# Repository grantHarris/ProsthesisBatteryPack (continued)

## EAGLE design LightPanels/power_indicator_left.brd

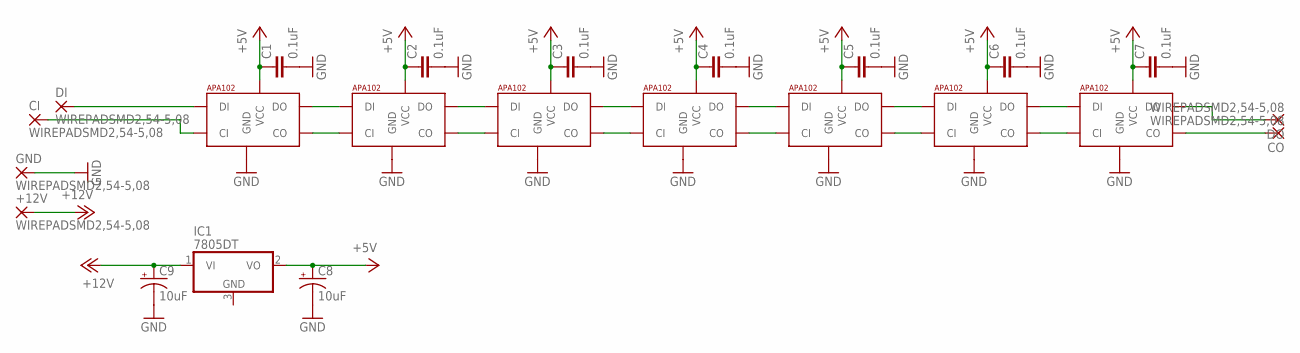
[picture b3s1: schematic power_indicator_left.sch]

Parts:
+12V: WIREPADSMD2,54-5,08; SMD2,54-5,08
C1, C2, C3, C4, C5, C6, C7: 0.1uF; 0603-CAP
C8, C9: 10uF; EIA3216
CI: WIREPADSMD2,54-5,08; SMD2,54-5,08
CO: WIREPADSMD2,54-5,08; SMD2,54-5,08
DI: WIREPADSMD2,54-5,08; SMD2,54-5,08
DO: WIREPADSMD2,54-5,08; SMD2,54-5,08
GND: WIREPADSMD2,54-5,08; SMD2,54-5,08
IC1: 7805DT; TO252
U$1, U$2, U$3, U$4, U$5, U$6, U$7: APA1025050; APA102_5050

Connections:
+5V: C1.1, C2.1, C3.1, C4.1, C5.1, C6.1, C7.1, C8.A (+), IC1.2 (VO), U$1.1 (VCC), U$2.1 (VCC), U$3.1 (VCC), U$4.1 (VCC), U$5.1 (VCC), U$6.1 (VCC), U$7.1 (VCC)
+12V: +12V.1, C9.A (+), IC1.1 (VI)
GND: C1.2, C2.2, C3.2, C4.2, C5.2, C6.2, C7.2, C8.C (-), C9.C (-), GND.1, U$1.6 (GND), U$2.6 (GND), U$3.6 (GND), U$4.6 (GND), U$5.6 (GND), U$6.6 (GND), U$7.6 (GND)
unnamed: U$1.2 (CO), U$2.5 (CI)
unnamed: U$1.3 (DO), U$2.4 (DI)
unnamed: U$2.2 (CO), U$3.5 (CI)
unnamed: U$2.3 (DO), U$3.4 (DI)
unnamed: U$3.2 (CO), U$4.5 (CI)
unnamed: U$3.3 (DO), U$4.4 (DI)
unnamed: U$4.2 (CO), U$5.5 (CI)
unnamed: U$4.3 (DO), U$5.4 (DI)
unnamed: U$5.2 (CO), U$6.5 (CI)
unnamed: U$5.3 (DO), U$6.4 (DI)
unnamed: U$6.2 (CO), U$7.5 (CI)
unnamed: U$6.3 (DO), U$7.4 (DI)
unnamed: CO.1, U$7.2 (CO)
unnamed: DO.1, U$7.3 (DO)
unnamed: DI.1, U$1.4 (DI)
unnamed: CI.1, U$1.5 (CI)

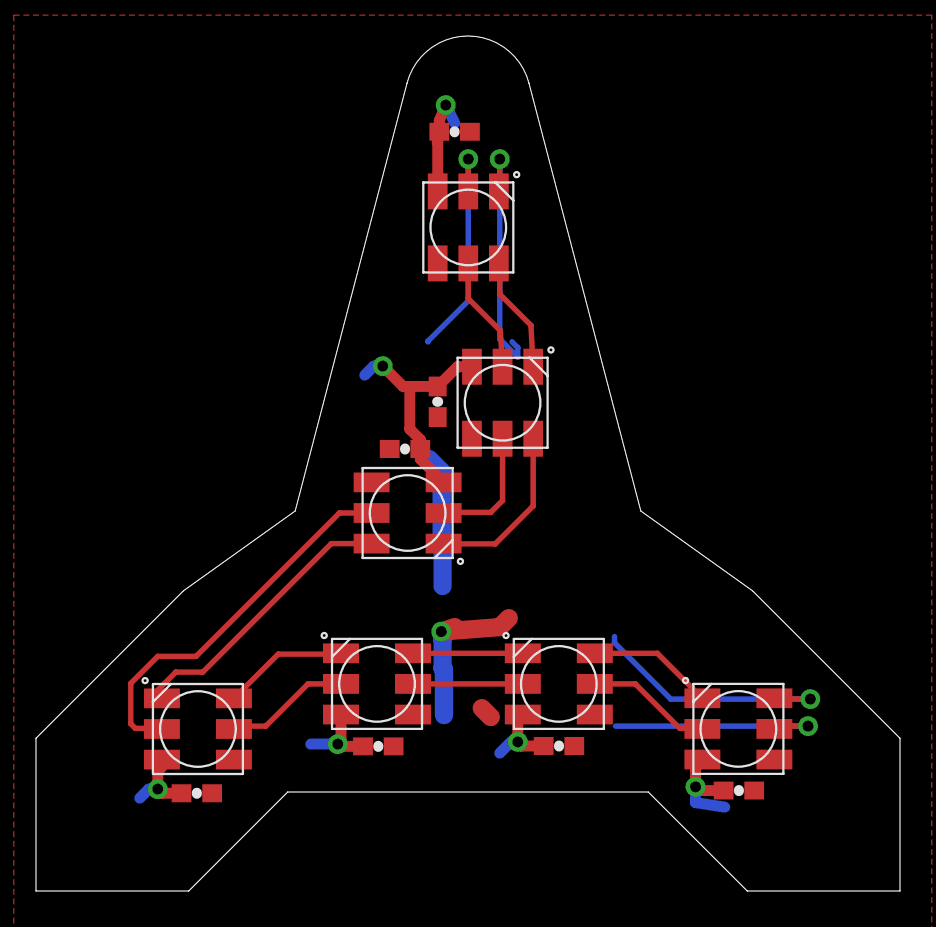
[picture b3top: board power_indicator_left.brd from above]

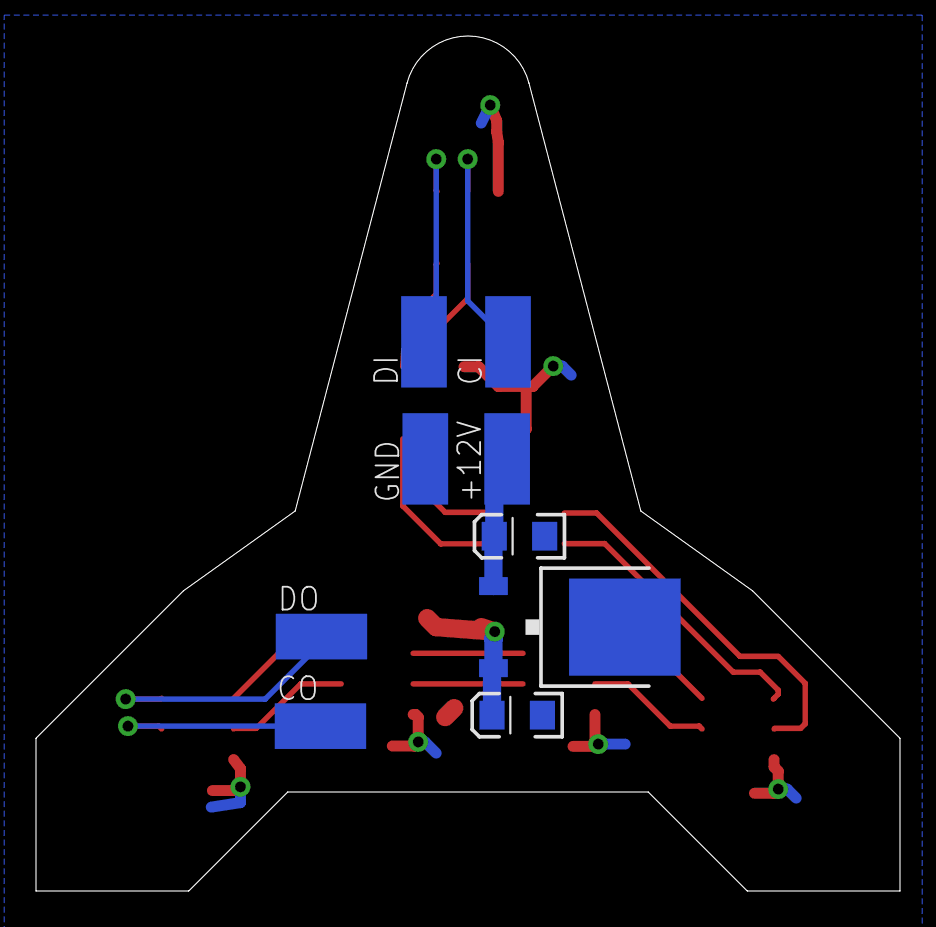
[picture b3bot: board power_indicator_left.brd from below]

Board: 2 copper layers, 48.0 x 47.5 mm, 23 parts (9 on the bottom side), 19 nets.

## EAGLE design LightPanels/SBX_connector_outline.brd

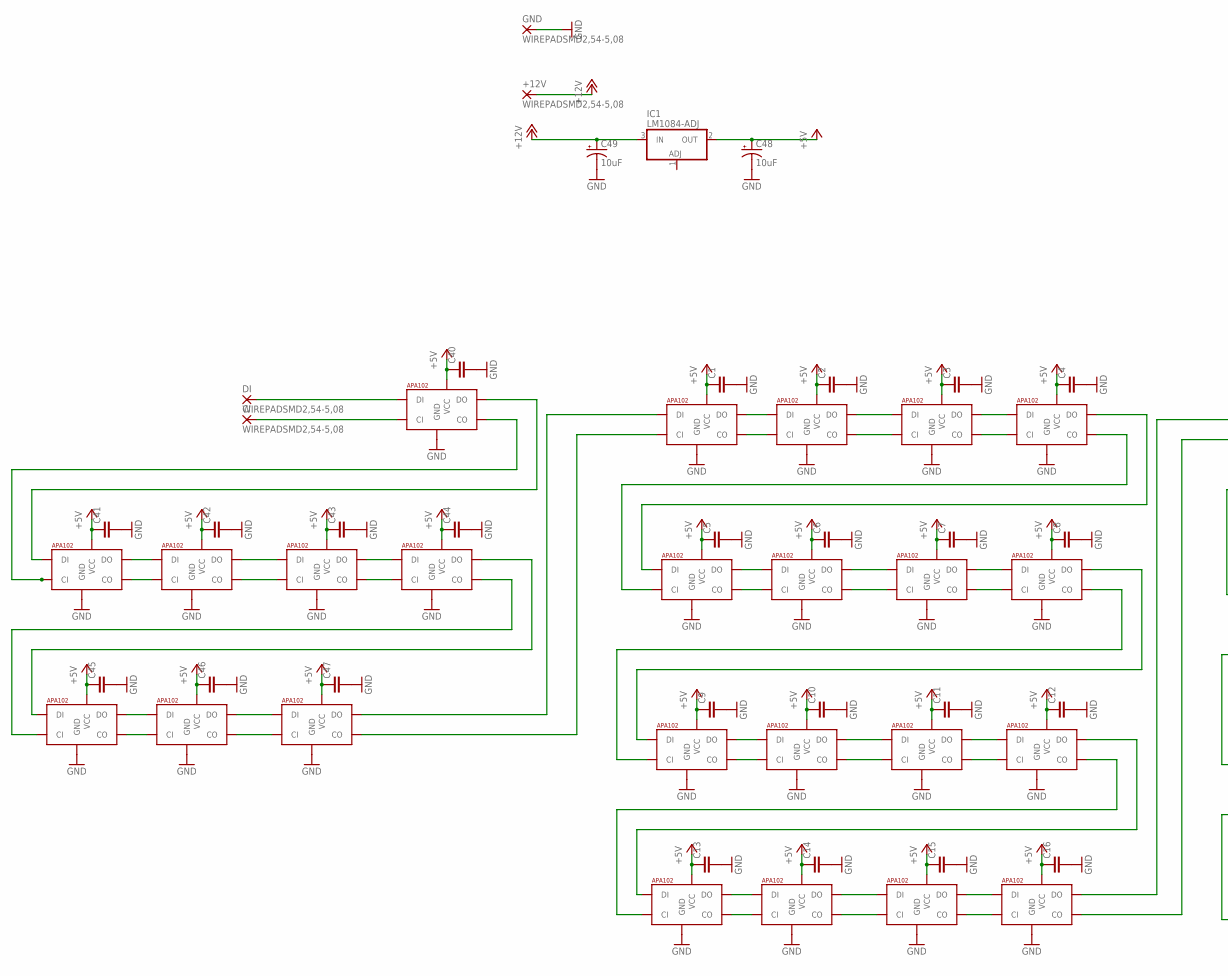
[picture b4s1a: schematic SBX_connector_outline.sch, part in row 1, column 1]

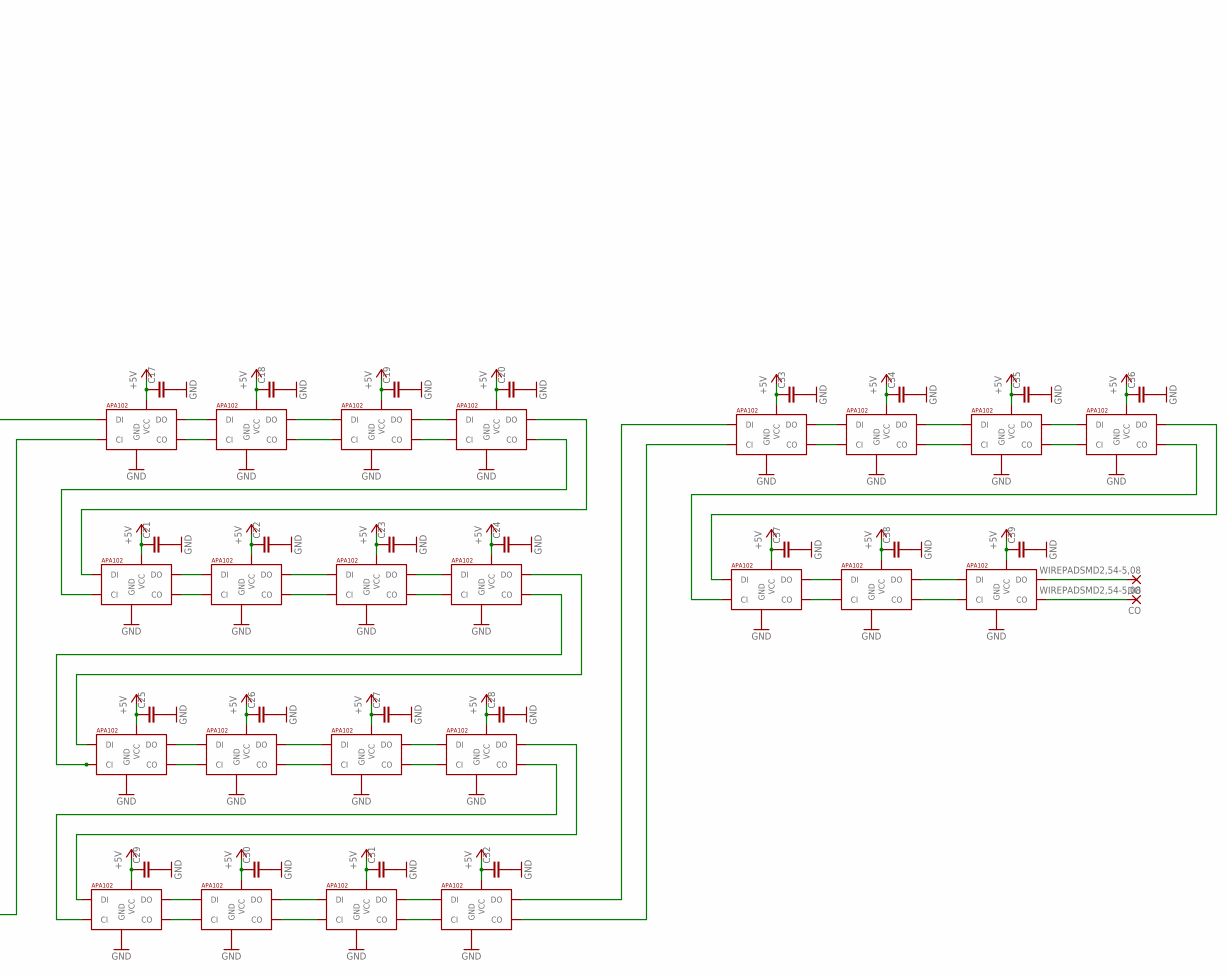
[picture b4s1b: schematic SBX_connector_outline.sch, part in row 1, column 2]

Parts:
+12V: WIREPADSMD2,54-5,08; SMD2,54-5,08
C1, C2, C3, C4, C5, C6, C7, C8, C9, C10, C11, C12, C13, C14, C15, C16, C17, C18, C19, C20, C21, C22, C23, C24, C25, C26, C27, C28, C29, C30, C31, C32, C33, C34, C35, C36, C37, C38, C39, C40, C41, C42, C43, C44, C45, C46, C47: CAP0603-CAP; 0603-CAP
C48, C49: 10uF; EIA3216
CI: WIREPADSMD2,54-5,08; SMD2,54-5,08
CO: WIREPADSMD2,54-5,08; SMD2,54-5,08
DI: WIREPADSMD2,54-5,08; SMD2,54-5,08
DO: WIREPADSMD2,54-5,08; SMD2,54-5,08
GND: WIREPADSMD2,54-5,08; SMD2,54-5,08
IC1: LM1084-ADJ; TO263-3
U$1, U$2, U$3, U$4, U$5, U$6, U$7, U$8, U$9, U$10, U$11, U$12, U$13, U$14, U$15, U$16, U$17, U$18, U$19, U$20, U$21, U$22, U$23, U$24, U$25, U$26, U$27, U$28, U$29, U$30, U$31, U$32, U$33, U$34, U$35, U$36, U$37, U$38, U$39, U$40, U$41, U$42, U$43, U$44, U$45, U$46, U$47: APA1025050; APA102_5050

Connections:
+5V: C1.1, C2.1, C3.1, C4.1, C5.1, C6.1, C7.1, C8.1, C9.1, C10.1, C11.1, C12.1, C13.1, C14.1, C15.1, C16.1, C17.1, C18.1, C19.1, C20.1, C21.1, C22.1, C23.1, C24.1, C25.1, C26.1, C27.1, C28.1, C29.1, C30.1, C31.1, C32.1, C33.1, C34.1, C35.1, C36.1, C37.1, C38.1, C39.1, C40.1, C41.1, C42.1, C43.1, C44.1, C45.1, C46.1, C47.1, C48.A (+), IC1.2 (OUT), U$1.1 (VCC), U$2.1 (VCC), U$3.1 (VCC), U$4.1 (VCC), U$5.1 (VCC), U$6.1 (VCC), U$7.1 (VCC), U$8.1 (VCC), U$9.1 (VCC), U$10.1 (VCC), U$11.1 (VCC), U$12.1 (VCC), U$13.1 (VCC), U$14.1 (VCC), U$15.1 (VCC), U$16.1 (VCC), U$17.1 (VCC), U$18.1 (VCC), U$19.1 (VCC), U$20.1 (VCC), U$21.1 (VCC), U$22.1 (VCC), U$23.1 (VCC), U$24.1 (VCC), U$25.1 (VCC), U$26.1 (VCC), U$27.1 (VCC), U$28.1 (VCC), U$29.1 (VCC), U$30.1 (VCC), U$31.1 (VCC), U$32.1 (VCC), U$33.1 (VCC), U$34.1 (VCC), U$35.1 (VCC), U$36.1 (VCC), U$37.1 (VCC), U$38.1 (VCC), U$39.1 (VCC), U$40.1 (VCC), U$41.1 (VCC), U$42.1 (VCC), U$43.1 (VCC), U$44.1 (VCC), U$45.1 (VCC), U$46.1 (VCC), U$47.1 (VCC)
+12V: +12V.1, C49.A (+), IC1.3 (IN)
GND: C1.2, C2.2, C3.2, C4.2, C5.2, C6.2, C7.2, C8.2, C9.2, C10.2, C11.2, C12.2, C13.2, C14.2, C15.2, C16.2, C17.2, C18.2, C19.2, C20.2, C21.2, C22.2, C23.2, C24.2, C25.2, C26.2, C27.2, C28.2, C29.2, C30.2, C31.2, C32.2, C33.2, C34.2, C35.2, C36.2, C37.2, C38.2, C39.2, C40.2, C41.2, C42.2, C43.2, C44.2, C45.2, C46.2, C47.2, C48.C (-), C49.C (-), GND.1, U$1.6 (GND), U$2.6 (GND), U$3.6 (GND), U$4.6 (GND), U$5.6 (GND), U$6.6 (GND), U$7.6 (GND), U$8.6 (GND), U$9.6 (GND), U$10.6 (GND), U$11.6 (GND), U$12.6 (GND), U$13.6 (GND), U$14.6 (GND), U$15.6 (GND), U$16.6 (GND), U$17.6 (GND), U$18.6 (GND), U$19.6 (GND), U$20.6 (GND), U$21.6 (GND), U$22.6 (GND), U$23.6 (GND), U$24.6 (GND), U$25.6 (GND), U$26.6 (GND), U$27.6 (GND), U$28.6 (GND), U$29.6 (GND), U$30.6 (GND), U$31.6 (GND), U$32.6 (GND), U$33.6 (GND), U$34.6 (GND), U$35.6 (GND), U$36.6 (GND), U$37.6 (GND), U$38.6 (GND), U$39.6 (GND), U$40.6 (GND), U$41.6 (GND), U$42.6 (GND), U$43.6 (GND), U$44.6 (GND), U$45.6 (GND), U$46.6 (GND), U$47.6 (GND)
unnamed: U$1.3 (DO), U$2.4 (DI)
unnamed: U$1.2 (CO), U$2.5 (CI)
unnamed: U$2.3 (DO), U$3.4 (DI)
unnamed: U$2.2 (CO), U$3.5 (CI)
unnamed: U$3.3 (DO), U$4.4 (DI)
unnamed: U$3.2 (CO), U$4.5 (CI)
unnamed: U$4.3 (DO), U$5.4 (DI)
unnamed: U$4.2 (CO), U$5.5 (CI)
unnamed: U$5.3 (DO), U$6.4 (DI)
unnamed: U$5.2 (CO), U$6.5 (CI)
unnamed: U$6.3 (DO), U$7.4 (DI)
unnamed: U$6.2 (CO), U$7.5 (CI)
unnamed: U$7.3 (DO), U$8.4 (DI)
unnamed: U$7.2 (CO), U$8.5 (CI)
unnamed: U$8.3 (DO), U$9.4 (DI)
unnamed: U$8.2 (CO), U$9.5 (CI)
unnamed: U$9.3 (DO), U$10.4 (DI)
unnamed: U$9.2 (CO), U$10.5 (CI)
unnamed: U$10.3 (DO), U$11.4 (DI)
unnamed: U$10.2 (CO), U$11.5 (CI)
unnamed: U$11.3 (DO), U$12.4 (DI)
unnamed: U$11.2 (CO), U$12.5 (CI)
unnamed: U$12.3 (DO), U$13.4 (DI)
unnamed: U$12.2 (CO), U$13.5 (CI)
unnamed: U$13.3 (DO), U$14.4 (DI)
unnamed: U$13.2 (CO), U$14.5 (CI)
unnamed: U$14.3 (DO), U$15.4 (DI)
unnamed: U$14.2 (CO), U$15.5 (CI)
unnamed: U$15.3 (DO), U$16.4 (DI)
unnamed: U$15.2 (CO), U$16.5 (CI)
unnamed: U$16.3 (DO), U$17.4 (DI)
unnamed: U$32.3 (DO), U$33.4 (DI)
unnamed: U$17.3 (DO), U$18.4 (DI)
unnamed: U$17.2 (CO), U$18.5 (CI)
unnamed: U$18.3 (DO), U$19.4 (DI)
unnamed: U$18.2 (CO), U$19.5 (CI)
unnamed: U$19.3 (DO), U$20.4 (DI)
unnamed: U$19.2 (CO), U$20.5 (CI)
unnamed: U$20.3 (DO), U$21.4 (DI)
unnamed: U$20.2 (CO), U$21.5 (CI)
unnamed: U$21.3 (DO), U$22.4 (DI)
unnamed: U$21.2 (CO), U$22.5 (CI)
unnamed: U$22.3 (DO), U$23.4 (DI)
unnamed: U$22.2 (CO), U$23.5 (CI)
unnamed: U$23.3 (DO), U$24.4 (DI)
unnamed: U$23.2 (CO), U$24.5 (CI)
unnamed: U$24.3 (DO), U$25.4 (DI)
unnamed: U$24.2 (CO), U$25.5 (CI)
unnamed: U$25.3 (DO), U$26.4 (DI)
unnamed: U$25.2 (CO), U$26.5 (CI)
unnamed: U$26.3 (DO), U$27.4 (DI)
unnamed: U$26.2 (CO), U$27.5 (CI)
unnamed: U$27.3 (DO), U$28.4 (DI)
unnamed: U$27.2 (CO), U$28.5 (CI)
unnamed: U$28.3 (DO), U$29.4 (DI)
unnamed: U$28.2 (CO), U$29.5 (CI)
unnamed: U$29.3 (DO), U$30.4 (DI)
unnamed: U$29.2 (CO), U$30.5 (CI)
unnamed: U$30.3 (DO), U$31.4 (DI)
unnamed: U$30.2 (CO), U$31.5 (CI)
unnamed: U$31.3 (DO), U$32.4 (DI)
unnamed: U$31.2 (CO), U$32.5 (CI)
unnamed: U$1.4 (DI), U$47.3 (DO)
unnamed: U$1.5 (CI), U$47.2 (CO)
unnamed: U$33.3 (DO), U$34.4 (DI)
unnamed: U$16.2 (CO), U$17.5 (CI)
unnamed: U$33.2 (CO), U$34.5 (CI)
unnamed: U$34.3 (DO), U$35.4 (DI)
unnamed: U$34.2 (CO), U$35.5 (CI)
unnamed: U$35.3 (DO), U$36.4 (DI)
unnamed: U$35.2 (CO), U$36.5 (CI)
unnamed: U$36.3 (DO), U$37.4 (DI)
unnamed: U$36.2 (CO), U$37.5 (CI)
unnamed: U$37.3 (DO), U$38.4 (DI)
unnamed: U$37.2 (CO), U$38.5 (CI)
unnamed: U$38.3 (DO), U$39.4 (DI)
unnamed: U$38.2 (CO), U$39.5 (CI)
unnamed: DO.1, U$39.3 (DO)
unnamed: CO.1, U$39.2 (CO)
unnamed: U$40.3 (DO), U$41.4 (DI)
unnamed: U$40.2 (CO), U$41.5 (CI)
unnamed: U$41.3 (DO), U$42.4 (DI)
unnamed: U$41.2 (CO), U$42.5 (CI)
unnamed: U$42.3 (DO), U$43.4 (DI)
unnamed: U$42.2 (CO), U$43.5 (CI)
unnamed: U$43.3 (DO), U$44.4 (DI)
unnamed: U$43.2 (CO), U$44.5 (CI)
unnamed: U$44.3 (DO), U$45.4 (DI)
unnamed: U$44.2 (CO), U$45.5 (CI)
unnamed: U$45.3 (DO), U$46.4 (DI)
unnamed: U$45.2 (CO), U$46.5 (CI)
unnamed: U$46.3 (DO), U$47.4 (DI)
unnamed: U$46.2 (CO), U$47.5 (CI)
unnamed: CI.1, U$40.5 (CI)
unnamed: DI.1, U$40.4 (DI)
unnamed: U$32.2 (CO), U$33.5 (CI)

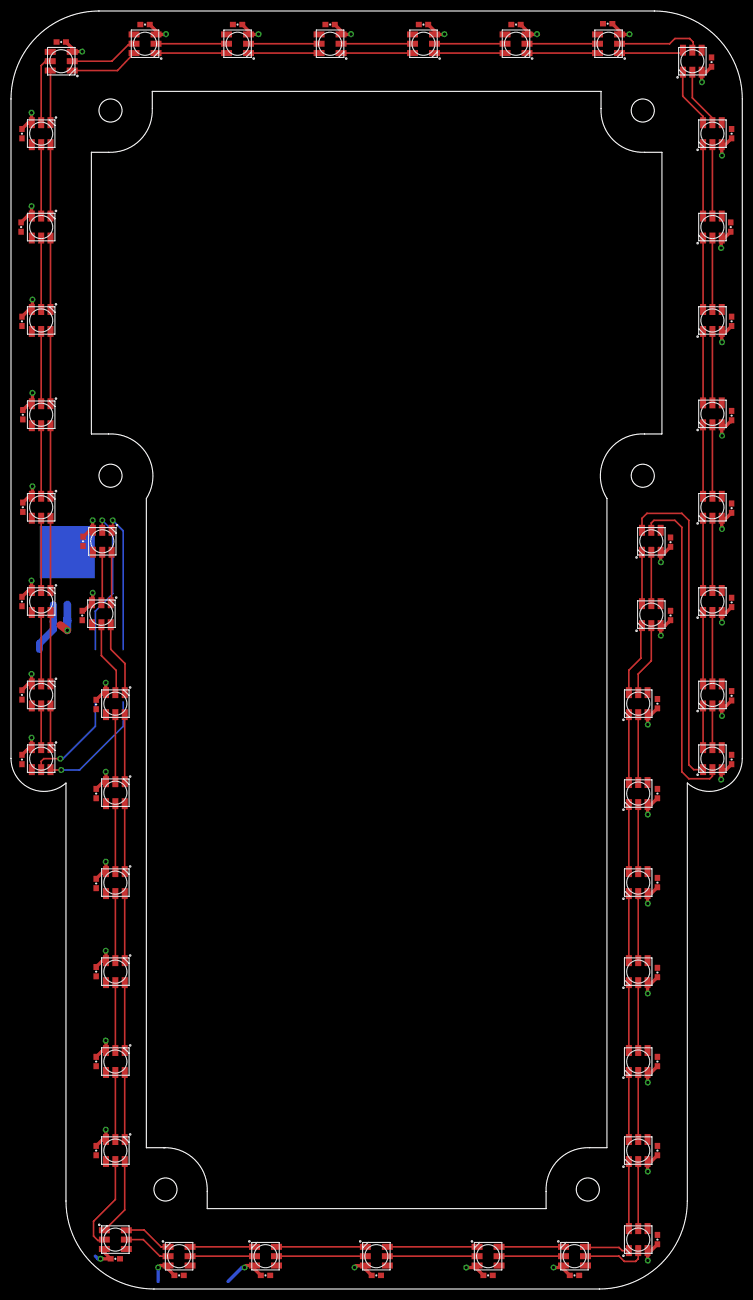
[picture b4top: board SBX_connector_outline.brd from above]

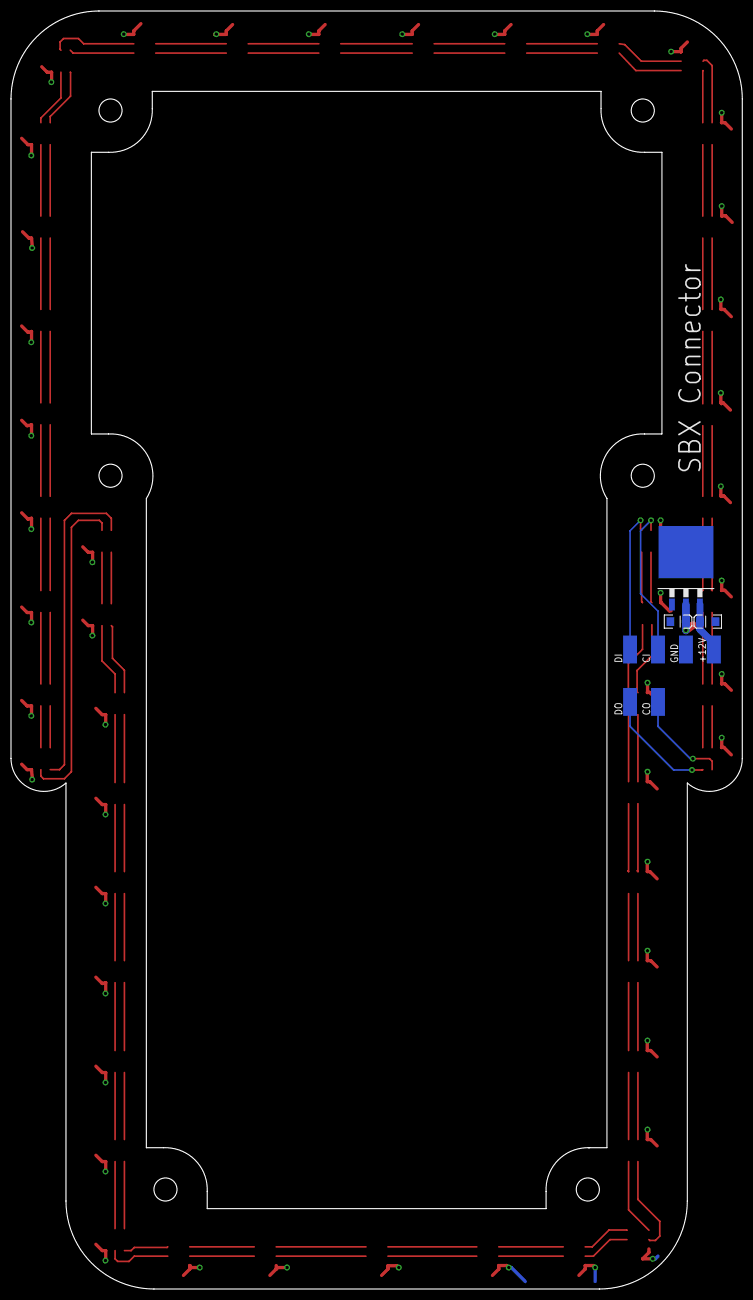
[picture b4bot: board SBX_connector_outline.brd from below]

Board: 2 copper layers, 133.0 x 232.4 mm, 103 parts (9 on the bottom side), 99 nets.

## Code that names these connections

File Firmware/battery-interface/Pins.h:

//Buzzer
#define BUZZER_PIN 10

//Fan PWM Pin
#define FAN_PWM_PIN 23

//SBX Sense
#define SBX_SENSE_RIGHT_PIN 7
#define SBX_SENSE_LEFT_PIN 8

//Contactor Closed Sense
#define CONTACTOR_SENSE_RIGHT_PIN 19
#define CONTACTOR_SENSE_LEFT_PIN 18

//Precharge Enable Sense
#define PRECHARGE_EN_SENSE_RIGHT_PIN 17
#define PRECHARGE_EN_SENSE_LEFT_PIN 16

//Charge Sense
#define CHARGE_SENSE_RIGHT_PIN 15
#define CHARGE_SENSE_LEFT_PIN 14

//LED
#define LED_DATA_PIN     11
#define LED_CLOCK_PIN    13

//Fan LED Strip
#define FAN_R_PIN 9
#define FAN_G_PIN 6
#define FAN_B_PIN 5

//Pack LED Strip
#define PACK_R_PIN 20
#define PACK_G_PIN 21
#define PACK_B_PIN 22

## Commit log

2016-11-01 Existing boards
2016-11-01 DXf's
2016-11-01 CANShield
2016-11-02 No airwires
2016-11-12 SOC level indicator
2016-11-12 Updated SOC_level_indicator
2016-11-12 Latest light panel pcb files
2016-11-13 Power indicators more or less done
2016-11-14 Right connector rename and fix up import
2016-11-15 SBX_connector_outline board complete
2016-11-16 Clean up light panels. Remvoe names/values
2016-11-26 Can shield
2016-11-26 Most of the base board finished
2016-12-01 precharge progress
2016-12-05 down to one airwire
2016-12-05 Mostly done
2016-12-07 Feature complete pcb
2016-12-23 Firmware
2016-12-23 latest
2016-12-23 Update CAN addresses and make isCurrent work properly
2016-12-23 Split out age calc into own fn
2016-12-23 Add getters for inputs
2016-12-24 Invert charged state
2016-12-24 Enable all loops
2016-12-27 Battery Pack LED Indicators - mapping SOC and SXB Indicators, LED sections and block color fill
2016-12-28 Add SBX support. Rename SBX1 to SBX Right, SBX 2 to SBX Left
2016-12-28 Inputs for precharge en should not be inverted
2016-12-30 Grant's unfinished work on indicators
2017-03-07 Can relay board partially done
